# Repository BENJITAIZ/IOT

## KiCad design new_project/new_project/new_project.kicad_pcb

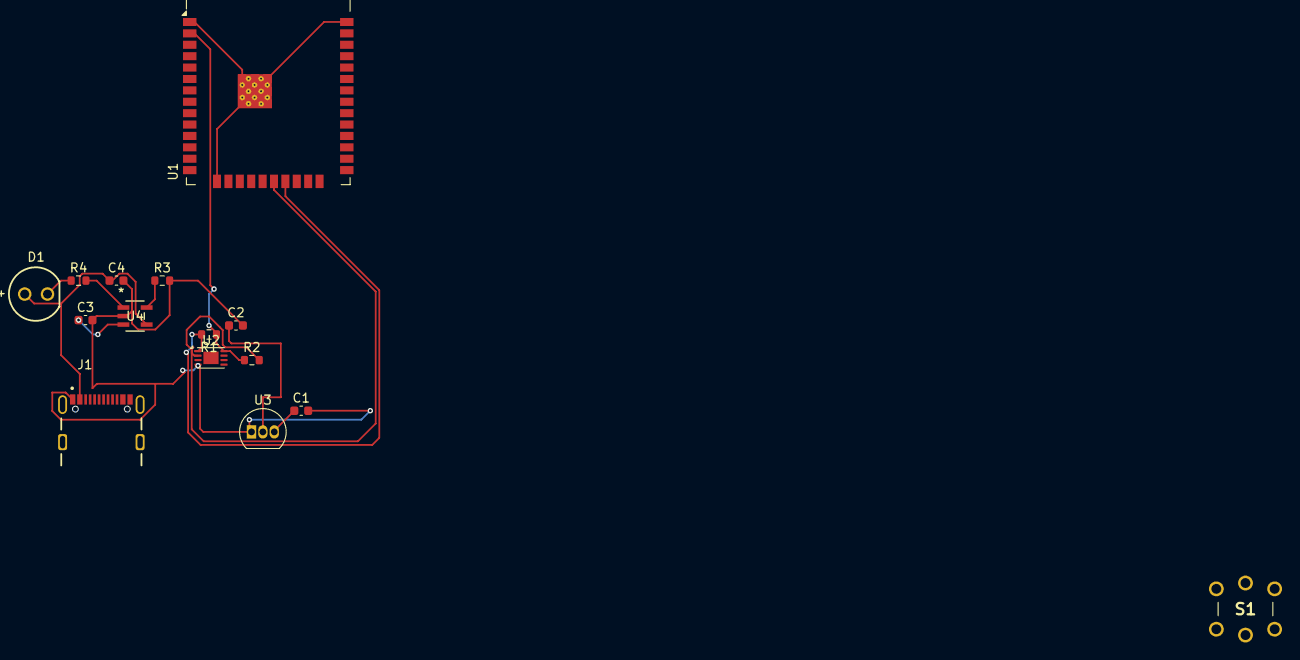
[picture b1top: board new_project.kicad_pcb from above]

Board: 2 copper layers, 15 parts (0 on the bottom side), 12 nets.

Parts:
C1, C2, C3, C4: C; C_0603_1608Metric
D1: WL-TMRC_5MM
J1: USB4105GFA120; GCT_USB4105GFA120
R1, R2, R3, R4: R; R_0603_1608Metric
S1: ILS_TA180_60; ILSTA18060
U1: ESP32-WROOM-32D
U2: MCP9808_DFN; DFN-8-1EP_3x2mm_P0.5mm_EP1.7x1.4mm
U3: MCP1700x-330xxTO; TO-92_Inline
U4: MCP73831T-2DCI/OT; SOT-23-5_MC_MCH

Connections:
+3.3V: R1.1, R2.1, U1.2 (VDD), U2.8 (V_{DD})
GND: C1.2, C2.2, C3.2, C4.2, J1.A1_B12 (GND), R3.2, U2.4 (GND), U3.1 (GND), U4.2 (VSS)
unnamed: D1.2, R4.1
unnamed: C4.1, D1.1, J1.A4_B9 (VBUS), U4.4 (VDD)
unnamed: U1.1 (GND), U1.15 (GND), U1.38 (GND), U1.39 (GND)
unnamed: R2.2, U1.20 (SCK/CLK), U2.2 (SCL)
unnamed: R1.2, U1.21 (SDO/SD0), U2.1 (SDA)
unnamed: C1.1, U3.3 (VO)
unnamed: R3.1, U4.5 (PROG)
unnamed: R4.2, U4.1 (STAT)
unnamed: C3.1, U4.3 (VBAT)
vbat: C2.1, U3.2 (VI)
